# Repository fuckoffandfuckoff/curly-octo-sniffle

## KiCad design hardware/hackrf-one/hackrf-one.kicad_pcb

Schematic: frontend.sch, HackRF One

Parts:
C1, C3, C5, C7, C10, C11, C16, C19, C22, C24, C29, C30, C33, C34, C35, C36, C37, C38, C39, C40, C45, C47, C54, C55, C56, C57, C60, C63, C65, C66, C67: 33pF; GSG-0402; Part Number GRM1555C1H330JA01D
C2, C4, C6, C162, C163: 10nF; GSG-0402; Part Number GRM155R71C103KA01D
C8, C21, C32, C43, C48, C51: 22pF; GSG-0402; Part Number GRM1555C1H220JA01D
C9, C17, C18, C20, C23, C25, C28, C31, C44, C46, C49, C50, C58, C59, C61, C62, C64, C166: 100nF; GSG-0402; Part Number GRM155R61A104KA01D
C12, C13: 330pF; GSG-0402; Part Number GRM155R71H331KA01D
C14: 8p2; GSG-0402; Part Number UMK105CG8R2DV-F
C15: 180pF; GSG-0402; Part Number GRM1555C1H181JA01D
C26, C27: 47pF; GSG-0402; Part Number GRM1555C1H470JA01D
C41, C42, C52, C70, C160: 100pF; GSG-0402; Part Number GRM1555C1H101JA01D
C53, C161, C171: 1uF; GSG-0402; Part Number LMK105BJ105KV-F
D1: GSG-DIODE-TVS-BI; GSG-0402; Part Number LXES15AAA1-100
J2: RF-SHIELD-FRAME; GSG-SHIELD-BMI-S-230; Part Number BMI-S-230-F-R
J3: RF-SHIELD-COVER; GSG-NULL-MODULE; Part Number BMI-S-230-C
J4, J5, J6, J7, J8, J9: MOUNTING_HOLE; GSG-HOLE126MIL-COPPER
J10: GND_CLIP; GSG-TEST-POINT-S1751-46R; Part Number S1751-46R
L1, L4: DNP; GSG-0402
L2, L3, L5, L12, L13: 10uH; GSG-0603; Part Number BRL1608T100M
P4: ANTENNA; GSG-SMA-73251-2120; Part Number 73251-2121
P6: GPO4; GSG-TESTPOINT-50MIL
P7: GPO2; GSG-TESTPOINT-50MIL
P13: GPO1; GSG-TESTPOINT-50MIL
P17: GPO6; GSG-TESTPOINT-50MIL
P19: GPO3; GSG-TESTPOINT-50MIL
P21: REF_IN; GSG-TESTPOINT-50MIL
P27: MIXER_SDATA; GSG-TESTPOINT-50MIL
P31: MIXER_SCLK; GSG-TESTPOINT-50MIL
P32: MIXER_ENX; GSG-TESTPOINT-50MIL
P33: MIXER_RESETX; GSG-TESTPOINT-50MIL
P34: MIX_BYPASS; GSG-TESTPOINT-50MIL
P35: !MIX_BYPASS; GSG-TESTPOINT-50MIL
P42: TX; GSG-TESTPOINT-50MIL
P43: RX; GSG-TESTPOINT-50MIL
P44: HP; GSG-TESTPOINT-50MIL
P45: LP; GSG-TESTPOINT-50MIL
P46: TX_MIX_BP; GSG-TESTPOINT-50MIL
P47: RX_MIX_BP; GSG-TESTPOINT-50MIL
P48: TX_AMP; GSG-TESTPOINT-50MIL
P49: RX_AMP; GSG-TESTPOINT-50MIL
P50: AMP_BYPASS; GSG-TESTPOINT-50MIL
P51: !TX_AMP_PWR; GSG-TESTPOINT-50MIL
P52: !RX_AMP_PWR; GSG-TESTPOINT-50MIL
Q1, Q2, Q4: MOSFET_P; SOT23-3; Part Number BSS84
R1, R2: 470; GSG-0402; Part Number RMCF0402JT470R
R3: 22k; GSG-0402; Part Number ERJ-2GEJ223X
R4: 51k; GSG-0402; Part Number RMCF0402FT51K0
R5, R6, R24, R29, R36: 10k; GSG-0402; Part Number RMCF0402JT10K0
T1: MIX_IN_BALUN; GSG-B0310J50100AHF; Part Number B0310J50100AHF
T2: MIX_OUT_BALUN; GSG-B0310J50100AHF; Part Number B0310J50100AHF
U1, U2, U5, U6, U7, U10, U11: SKY13350; GSG-SKY13350-385LF; Part Number SKY13350-385LF
U3: RX_LOWPASS_FILTER; GSG-LP0603; Part Number LP0603A1880ANTR
U4: RFFC5072; GSG-QFN32; Part Number RFFC5072TR7
U8: RX_HIGHPASS_FILTER; GSG-HP-DEA; Part Number DEA162400HT-8004B1
U9, U12, U14: SKY13317; GSG-SKY13317-373LF; Part Number SKY13317-373LF
U13, U25: MGA-81563; GSG-SOT363; Part Number MGA-81563-TR1G

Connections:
!MIX_BYPASS: C16.1, C38.2, C47.2, P35.1, U1.1, U9.6 (V2), U11.5; also elsewhere on the board
!RX_AMP_PWR: P52.1, Q1.1, R29.2; also elsewhere on the board
!TX_AMP_PWR: P51.1, Q2.1, R24.1; also elsewhere on the board
/frontend/!ANT_BIAS: P13.1, Q4.1, R36.1, U4.15 (GPO1/ADD1)
/frontend/REF_IN: C67.2, C70.1, P21.1, U4.10 (REF_IN)
/frontend/RX_AMP_IN: C58.1, U14.8 (RF3)
/frontend/RX_AMP_OUT: C50.2, U12.4 (RF1)
/frontend/TX_AMP_IN: C59.1, U12.8 (RF3)
/frontend/TX_AMP_OUT: C62.1, U14.4 (RF1)
AMP_BYPASS: C57.1, C65.2, P50.1, U12.6 (V2), U14.6 (V2); also elsewhere on the board
GND: C1.2, C2.2, C3.2, C4.2, C5.2, C6.2, C7.1, C10.1, C11.1, C12.2, C13.2, C16.2, C19.1, C22.1, C24.1, C25.2, C29.2, C30.2, C33.2, C34.2, C35.2, C36.2, C37.2, C38.1, C39.1, C40.1, C41.2, C42.2, C45.1, C47.1, C49.1, C52.2, C53.2, C54.2, C55.2, C56.2, C57.2, C60.1, C63.2, C65.1, C66.1, C70.2, C160.2, C161.2, C162.1, C163.1, C166.2, C171.2, D1.1 (A), J2.0, J4.1, J5.1, J6.1, J7.1, J8.1, J9.1, J10.1, P4.2 (GND), R4.1, U1.3, U2.3, U3.2 (GND), U3.3 (GND), U4.0 (EP), U4.12 (TM), U5.3, U6.3, U7.3, U8.2 (GND), U8.4 (GND), U9.0 (GND), U10.3, U11.3, U12.0 (GND), U13.1, U13.2, U13.4, U13.5, U14.0 (GND), U25.1, U25.2, U25.4, U25.5; also elsewhere on the board
HP: C29.1, C30.1, P44.1, U5.5, U6.1; also elsewhere on the board
LP: C11.2, C19.2, P45.1, U5.1, U6.5; also elsewhere on the board
MIXER_ENX: C35.1, P32.1, R6.2, U4.30 (ENX); also elsewhere on the board
MIXER_RESETX: C34.1, P33.1, R5.2, U4.29 (RESETX); also elsewhere on the board
MIXER_SCLK: C36.1, P31.1, U4.31 (SCLK); also elsewhere on the board
MIXER_SDATA: C37.1, P27.1, U4.32 (SDATA); also elsewhere on the board
MIX_BYPASS: C7.2, C56.1, P34.1, U1.5, U11.1; also elsewhere on the board
MIX_CLK: C67.1; also elsewhere on the board
unnamed: C8.2, U1.6
unnamed: C9.1, U7.2
unnamed: C9.2, U2.2
unnamed: C12.1, R1.2, U4.8 (LFILT3)
unnamed: C13.1, R1.1, R2.2
unnamed: C14.1, C15.1, R2.1, U4.7 (LFITLT2)
unnamed: C14.2, R3.1, U4.6 (LFILT1)
unnamed: C15.2, R3.2
unnamed: C17.1, U3.4 (IN)
unnamed: C17.2, U6.4
unnamed: C18.1, U5.2
unnamed: C18.2, U3.1 (OUT)
unnamed: C20.1, U6.6
unnamed: C20.2, U2.6
unnamed: C21.1, U1.2
unnamed: C21.2, U7.4
unnamed: C23.1, U10.4
unnamed: C23.2, U2.4
unnamed: C25.1, T1.2 (S2)
unnamed: C26.1, U8.3 (OUT)
unnamed: C26.2, U5.4
unnamed: C27.1, U8.1 (IN)
unnamed: C27.2, U6.2
unnamed: C28.1, T1.1 (S1)
unnamed: C28.2, U7.6
unnamed: C31.1, U9.5 (RF2)
unnamed: C31.2, U5.6
unnamed: C32.1, U1.4
unnamed: C32.2, U9.4 (RF1)
unnamed: C43.1, U9.8 (RF3)
unnamed: C43.2, U11.2
unnamed: C44.1, U12.1 (RFC)
unnamed: C44.2, U9.1 (RFC)
unnamed: C46.1, U10.6
unnamed: C46.2, T2.1 (S1)
unnamed: C48.1, U11.6
unnamed: C49.2, T2.2 (S2)
unnamed: C50.1, L5.2, U13.6
unnamed: C51.1, U11.4
unnamed: C51.2, U10.2
unnamed: C58.2, U13.3
unnamed: C59.2, U25.3
unnamed: C61.1, U14.5 (RF2)
unnamed: C61.2, U12.5 (RF2)
unnamed: C62.2, L12.2, U25.6
unnamed: C64.1, U14.1 (RFC)
unnamed: C64.2, D1.2 (K), L13.2, P4.1 (RF)
unnamed: C160.1, C162.2, L12.1, Q2.3
unnamed: C52.1, C163.2, L5.1, Q1.3
unnamed: L1.1, T1.4 (PR2), U4.23 (MIX_IPP)
unnamed: L1.2, T1.3 (PR1), U4.24 (MIX_IPN)
unnamed: L2.1, L4.2, T2.4 (PR2), U4.27 (MIX_OPN)
unnamed: L3.1, L4.1, T2.3 (PR1), U4.28 (MIX_OPP)
unnamed: L13.1, Q4.3
unnamed: P6.1, U4.26 (GPO4/LD/DO)
unnamed: P7.1, U4.16 (GPO2/ADD2)
unnamed: P17.1, U4.9 (MODE/GPO6)
unnamed: P19.1, U4.25 (GPO3/FM)
unnamed: R4.2, U4.4 (REXT)
RX: C10.2, C22.2, C54.1, P43.1, U2.1, U7.1, U10.1; also elsewhere on the board
RX_AMP: C60.2, C66.2, P49.1, U12.3 (V1), U14.7 (V3); also elsewhere on the board
RX_IF: C48.2; also elsewhere on the board
RX_MIX_BP: C40.2, P47.1, U9.7 (V3); also elsewhere on the board
TX: C24.2, C33.1, C45.2, P42.1, U2.5, U7.5, U10.5; also elsewhere on the board
TX_AMP: C55.1, C63.1, P48.1, U12.7 (V3), U14.3 (V1); also elsewhere on the board
TX_IF: C8.1; also elsewhere on the board
TX_MIX_BP: C39.2, P46.1, U9.3 (V1); also elsewhere on the board
VAA: C3.1, C4.1, C5.1, C6.1, C41.1, C42.1, C53.1, C161.1, C166.1, C171.1, L2.2, L3.2, Q1.2, Q2.2, Q4.2, R24.2, R29.1, R36.2, U4.5 (ANA_VDD1), U4.22 (ANA_VDD2); also elsewhere on the board
VCC: C1.1, C2.1, R5.1, R6.1, U4.19 (DIG_VDD); also elsewhere on the board

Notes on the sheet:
amplifier bypass path
switchable image reject filters
Expected MIX_CLK is 1.8 to 3.3 V peak-to-peak at 25 to 52 MHz. It is divided down to 0.5 to 1.5 V (REF_IN).
loop filter
mounting holes are connected to GND
optional alligator clip test point

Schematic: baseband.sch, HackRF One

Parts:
C68, C69, C90, C159, C165, C168: 100pF; GSG-0402; Part Number GRM1555C1H101JA01D
C71, C73, C75, C77, C79, C81, C83, C91, C113, C119, C120, C121, C122, C123, C167: 100nF; GSG-0402; Part Number GRM155R61A104KA01D
C72, C74, C76, C78, C80, C82, C124: 2.2uF; GSG-0402; Part Number LMK105BJ225MV-F
C84, C85, C86, C94, C95, C96, C99, C101, C102, C103, C107, C108, C109, C110: 22pF; GSG-0402; Part Number GRM1555C1H220JA01D
C87, C88, C89, C92, C93: 10nF; GSG-0402; Part Number GRM155R71C103KA01D
C97, C98, C100: 330nF; GSG-0402; Part Number GRM155R61A334KE15D
C104, C111: 3pF; GSG-0402; Part Number GRM1555C1H3R0CA01D
C105: 10uF; GSG-0805; Part Number GRM21BR61A106KE19L
C106: 1uF; GSG-0402; Part Number LMK105BJ105KV-F
C112: 180pF; GSG-0402; Part Number GRM1555C1H181JA01D
C114: 3.3nF; GSG-0402; Part Number GRM155R71H332KA01D
C115: 33pF; GSG-0402; Part Number GRM1555C1H330JA01D
C116: 47pF; GSG-0402; Part Number GRM1555C1H470JA01D
C169, C170: 1.8pF; GSG-0402; Part Number GRM1555C1E1R8BA01D
D3, D9: GSG-DIODE-TVS-BI; GSG-0402; Part Number LXES15AAA1-100
FB2: FILTER; GSG-0805; Part Number BLM21PG221SN1D
L6, L8, L9: DNP; GSG-0402
L7: 6.2nH; GSG-0402; Part Number HK10056N2S-T
NT3: VAA; HEADER-1x2-SHORTED
P2: CLKOUT; GSG-SMA-73251-2120; Part Number 73251-2121
P9: BASEBAND; GSG-HEADER-2x8; Part Number PPPC082LFBN-RC
P14: XCVR_CLKOUT; GSG-TESTPOINT-50MIL
P15: INTR; GSG-TESTPOINT-50MIL
P16: CLKIN; GSG-SMA-73251-2120; Part Number 73251-2121
P18: OEB; GSG-TESTPOINT-50MIL
P37: SCL; GSG-TESTPOINT-50MIL
P38: SDA; GSG-TESTPOINT-50MIL
P39: SSP1_SCK; GSG-TESTPOINT-50MIL
P40: SSP1_COPI; GSG-TESTPOINT-50MIL
P41: SSP1_CIPO; GSG-TESTPOINT-50MIL
P53: CS_XCVR; GSG-TESTPOINT-50MIL
P54: CS_AD; GSG-TESTPOINT-50MIL
P55: TXENABLE; GSG-TESTPOINT-50MIL
P56: RXENABLE; GSG-TESTPOINT-50MIL
P57: XTAL2; GSG-TESTPOINT-50MIL
P58: GCK1; GSG-TESTPOINT-50MIL
P59: GCK2; GSG-TESTPOINT-50MIL
P60: SGPIO_CLK; GSG-TESTPOINT-50MIL
P61: DA0; GSG-TESTPOINT-50MIL
P62: DA7; GSG-TESTPOINT-50MIL
P63: DD0; GSG-TESTPOINT-50MIL
P64: DD9; GSG-TESTPOINT-50MIL
P65: DA4; GSG-TESTPOINT-50MIL
P66: DD5; GSG-TESTPOINT-50MIL
P67: RSSI; GSG-TESTPOINT-50MIL
P83, P84, P85, P86, P87, P88, P89, P90, P91, P92: GND; GSG-TESTPOINT-50MIL
Q3: MOSFET_P; SOT23-3; Part Number DMP2305U-7
R8, R9, R10, R13: 1k; GSG-0402; Part Number RMCF0402FT1K00
R11, R41, R85, R104, R105: 10k; GSG-0402; Part Number RMCF0402JT10K0
R14, R15, R16, R17: 4k7; GSG-0402; Part Number RMCF0402FT4K70
R20, R21, R22, R23: 0; GSG-0402; Part Number RMCF0402ZT0R00
R25, R26: 475; GSG-0402; Part Number RMCF0402JT470R
R27, R28: 1k8; GSG-0402; Part Number RMCF0402JT1K80
R31, R32, R33, R94: 39; GSG-0402; Part Number RMCF0402JT39R0
T3: RX_BALUN; GSG-2500BL14M100; Part Number 2500BL14M100T
T4: TX_BALUN; GSG-2500BL14M100; Part Number 2500BL14M100T
U17: MAX2837; GSG-QFN48-6; Part Number MAX2837ETM+
U18: MAX5864; GSG-QFN48-7; Part Number MAX5864ETM+
U19: SI5351C; GSG-QFN20-4; Part Number SI5351C-B-GM
X1: GSG-XTAL4PIN; GSG-XTAL3.2x2.5mm; Part Number ABM8-25.000MHZ-10-D1G-T

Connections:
!VAA_ENABLE: Q3.1, R11.2; also elsewhere on the board
/baseband/CLK0: R31.2, U19.13 (CLK0)
/baseband/CLK1: R32.2, U19.12 (CLK1)
/baseband/CLK2: R94.2, U19.9 (CLK2)
/baseband/CLK3: R33.2, U19.8 (CLK3)
/baseband/CLK5: C115.1, U19.17 (CLK5)
/baseband/COM: C97.1, U18.47 (COM)
/baseband/CPOUT+: C112.2, R25.1, U17.23 (CPOUT+)
/baseband/CPOUT-: C112.1, R26.1, U17.24 (CPOUT-)
/baseband/IA+: C101.1, C110.1, R20.1, U18.3 (IA+)
/baseband/IA-: C101.2, C109.1, R21.1, U18.4 (IA-)
/baseband/ID+: R13.1, U18.45 (ID+)
/baseband/ID-: R10.1, U18.44 (ID-)
/baseband/INTR: P15.1, R104.2, U19.3 (INTR)
/baseband/OEB: P18.1, R105.2, U19.7 (OEB)
/baseband/QA+: C103.2, C107.1, R23.1, U18.10 (QA+)
/baseband/QA-: C103.1, C108.1, R22.1, U18.9 (QA-)
/baseband/QD+: R8.1, U18.40 (QD+)
/baseband/QD-: R9.1, U18.41 (QD-)
/baseband/REFN: C98.1, U18.48 (REFN)
/baseband/REFP: C100.1, U18.1 (REFP)
/baseband/RXBBI+: P9.7, R20.2, U17.38 (RXBBI+)
/baseband/RXBBI-: P9.5, R21.2, U17.37 (RXBBI-)
/baseband/RXBBQ+: P9.6, R22.2, U17.36 (RXBBQ+)
/baseband/RXBBQ-: P9.4, R23.2, U17.35 (RXBBQ-)
/baseband/TXBBI+: C96.1, P9.12, R10.2, R15.1, U17.43 (TXBBI+)
/baseband/TXBBI-: C96.2, P9.10, R13.2, R14.1, U17.42 (TXBBI-)
/baseband/TXBBQ+: C95.2, P9.11, R9.2, R16.1, U17.44 (TXBBQ+)
/baseband/TXBBQ-: C95.1, P9.13, R8.2, R17.1, U17.45 (TXBBQ-)
/baseband/XA: C170.2, U19.1 (XA), X1.3
/baseband/XB: C169.2, U19.2 (XB), X1.1
/baseband/XCVR_CLKOUT: P14.1, U17.16 (CLOCKOUT)
/baseband/XTAL2: C115.2, C116.1, P57.1, U17.17 (XTAL2)
CLK6: U19.16 (CLK6); also elsewhere on the board
CLKIN: D3.2 (K), P16.1 (RF), R85.1, U19.6 (CLKIN); also elsewhere on the board
CLKOUT: C165.1, D9.2 (K), P2.1 (RF), R33.1; also elsewhere on the board
CS_AD: P54.1, U18.36 (CS); also elsewhere on the board
CS_XCVR: P53.1, U17.30 (CS); also elsewhere on the board
DA0: P61.1, U18.13 (DA0); also elsewhere on the board
DA1: U18.14 (DA1); also elsewhere on the board
DA2: U18.15 (DA2); also elsewhere on the board
DA3: U18.16 (DA3); also elsewhere on the board
DA4: P65.1, U18.19 (DA4); also elsewhere on the board
DA5: U18.20 (DA5); also elsewhere on the board
DA6: U18.21 (DA6); also elsewhere on the board
DA7: P62.1, U18.22 (DA7); also elsewhere on the board
DD0: P63.1, U18.23 (DD0); also elsewhere on the board
DD1: U18.24 (DD1); also elsewhere on the board
DD2: U18.25 (DD2); also elsewhere on the board
DD3: U18.26 (DD3); also elsewhere on the board
DD4: U18.27 (DD4); also elsewhere on the board
DD5: P66.1, U18.28 (DD5); also elsewhere on the board
DD6: U18.29 (DD6); also elsewhere on the board
DD7: U18.30 (DD7); also elsewhere on the board
DD8: U18.31 (DD8); also elsewhere on the board
DD9: P64.1, U18.32 (DD9); also elsewhere on the board
GCK1: C68.1, P58.1, R31.1, U18.6 (CLK); also elsewhere on the board
GCK2: C69.1, P59.1, R32.1; also elsewhere on the board
GND: C68.2, C69.2, C71.2, C72.2, C73.2, C74.2, C75.2, C76.2, C77.2, C78.2, C79.2, C80.2, C81.2, C82.2, C83.2, C84.2, C85.2, C86.2, C87.2, C88.2, C89.2, C90.2, C91.2, C92.2, C93.2, C94.2, C97.2, C98.2, C100.2, C105.2, C106.2, C107.2, C108.2, C109.2, C110.2, C113.2, C116.2, C119.2, C120.2, C121.2, C122.2, C123.2, C124.2, C159.2, C165.2, C167.2, C168.2, C169.1, C170.1, D3.1 (A), D9.1 (A), P2.2 (GND), P9.1, P9.2, P9.3, P9.8, P9.9, P9.14, P9.15, P9.16, P16.2 (GND), P83.1, P84.1, P85.1, P86.1, P87.1, P88.1, P89.1, P90.1, P91.1, P92.1, R14.2, R15.2, R16.2, R17.2, R41.1, R85.2, T3.2 (S2), T3.5 (PM), T4.2 (S2), T4.5 (PM), U17.0 (EP), U17.2 (GNDRXLNA), U17.22 (GNDCP), U17.26 (GNDVCO), U18.0 (EP), U18.5 (GND), U18.7 (GND), U18.12 (GND), U18.17 (OGND), U18.37 (GND), U18.42 (GND), U19.0 (GND), X1.2, X1.4; also elsewhere on the board
MCU_CLK: U19.15 (CLK7); also elsewhere on the board
MIX_CLK: U19.19 (CLK4); also elsewhere on the board
unnamed: C99.1, L7.1, U17.4 (RXRF+)
unnamed: C99.2, L6.1, T3.4 (PR2)
unnamed: C102.1, L7.2, U17.5 (RXRF-)
unnamed: C102.2, L6.2, T3.3 (PR1)
unnamed: C104.1, L9.1, U17.10 (TXRF+)
unnamed: C104.2, L8.1, T4.4 (PR2)
unnamed: C105.1, FB2.2, NT3.2
unnamed: C106.1, U17.27 (BYPASS)
unnamed: C111.1, L9.2, U17.11 (TXRF-)
unnamed: C111.2, L8.2, T4.3 (PR1)
unnamed: C114.1, R26.2
unnamed: C114.2, R25.2
unnamed: FB2.1, Q3.3
RSSI: P67.1, U17.32 (RSSI); also elsewhere on the board
RXENABLE: P56.1, U17.48 (RXENABLE); also elsewhere on the board
RX_IF: T3.1 (S1); also elsewhere on the board
SCL: P37.1, R28.2, U19.4 (SCL); also elsewhere on the board
SDA: P38.1, R27.2, U19.5 (SDA); also elsewhere on the board
SGPIO_CLK: C159.1, P60.1, R94.1; also elsewhere on the board
SSP1_CIPO: C168.1, P41.1, U17.29 (DOUT); also elsewhere on the board
SSP1_COPI: P40.1, U17.31 (DIN), U18.34 (DIN); also elsewhere on the board
SSP1_SCK: P39.1, U17.15 (SCLK), U18.35 (SCLK); also elsewhere on the board
TXENABLE: P55.1, U17.47 (TXENABLE); also elsewhere on the board
TX_IF: T4.1 (S1); also elsewhere on the board
VAA: C71.1, C72.1, C73.1, C74.1, C75.1, C76.1, C77.1, C78.1, C79.1, C80.1, C81.1, C82.1, C83.1, C84.1, C85.1, C86.1, C87.1, C89.1, C90.1, C91.1, C92.1, C93.1, C94.1, NT3.1, U17.1 (VCCRXLNA), U17.7 (VCCTXPAD), U17.13 (VCCTXMX), U17.19 (VCCXTAL), U17.21 (VCCCP), U17.28 (VCCVCO), U17.39 (VCCRXVGA), U17.41 (VCCRXFL), U17.46 (VCCRXMX), U18.2 (VDD), U18.8 (VDD), U18.11 (VDD), U18.33 (VDD), U18.39 (VDD), U18.43 (VDD), U18.46 (REFIN); also elsewhere on the board
VCC: C88.1, C113.1, C119.1, C120.1, C121.1, C122.1, C123.1, C124.1, C167.1, Q3.2, R11.1, R27.1, R28.1, R104.1, R105.1, U17.20 (VCCDIG), U18.18 (OVDD), U19.10 (VDDOB), U19.11 (VDDOA), U19.14 (VDDOD), U19.18 (VDDOC), U19.20 (VDD); also elsewhere on the board
XCVR_EN: R41.2, U17.25 (ENABLE); also elsewhere on the board

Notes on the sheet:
3.3 V CMOS clock output at 10 MHz (or other frequency with firmware modification)
3.3 V CMOS clock input at 10 MHz (or 10 MHz to 100 MHz with firmware modification)
test points
CLK0 is at the sample rate CLK1 is at sample rate x2 CLK2 is at sample rate x2

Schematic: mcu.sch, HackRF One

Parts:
C118, C157, C158, C164: 18pF; GSG-0402; Part Number GRM1555C1H180JA01D
C125: 33pF; GSG-0402; Part Number GRM1555C1H330JA01D
C126, C127, C143, C145, C146: 10uF; GSG-0805; Part Number GRM21BR61A106KE19L
C128, C129, C130, C131, C132, C133, C134, C135, C136, C137, C138, C139, C140, C141, C142, C144, C147, C148, C149, C150, C151, C152, C153, C154: 100nF; GSG-0402; Part Number GRM155R61A104KA01D
C155: DNP; GSG-0805
C156: 47pF; GSG-0402; Part Number GRM1555C1H470JA01D
D2: VAALED; LTST-S220; Part Number LTST-S220KRKT
D4: USBLED; LTST-S220; Part Number LTST-S220KGKT
D5: RXLED; LTST-S220; Part Number LTST-S220KSKT
D6: TXLED; LTST-S220; Part Number LTST-S220KRKT
D7: VCCLED; LTST-S220; Part Number LTST-S220KGKT
D8: 1V8LED; LTST-S220; Part Number LTST-S220KSKT
FB1, FB3: FILTER; GSG-0805; Part Number BLM21PG221SN1D
J1: USB-MICRO-B; GSG-USB-MICROB-FCI-10103592-EXT; Part Number 10103592-0001LF
L10, L11: 4u7; GSG-NRG4026; Part Number NRG4026T4R7M
NT1: 1V8; HEADER-1x2-SHORTED
NT2: VCC; HEADER-1x2-SHORTED
P3: GND; GSG-HEADER-NOMARK-1x2
P5: LEDS; GSG-HEADER-2x3
P20: GPIO; GSG-HEADER-2x11; Part Number PPPC112LFBN-RC
P22: I2S; GSG-HEADER-2x13; Part Number PPPC132LFBN-RC
P23: DBGEN; GSG-TESTPOINT-50MIL
P24: TRST; GSG-TESTPOINT-50MIL
P25: LPC_ISP; GSG-HEADER-1x6
P26: LPC_JTAG; GSG-50MIL-HEADER-2x5-TH; Part Number GRPB052VWVN-RC
P28: SD; GSG-HEADER-2x11; Part Number PPPC112LFBN-RC
P29: CPLD_JTAG; GSG-HEADER-1x2
P30: BANK2_AUX; GSG-HEADER-2x10
P68: SPIFI_CS; GSG-TESTPOINT-50MIL
P69: VREGMODE; GSG-TESTPOINT-50MIL
P70: EN_1V8; GSG-TESTPOINT-50MIL
P71: ID; GSG-TESTPOINT-50MIL
P72, P75, P76, P77, P78, P79: GP_CLKIN; GSG-TESTPOINT-50MIL
P73: P1_2; GSG-TESTPOINT-50MIL
P74: P1_1; GSG-TESTPOINT-50MIL
P80: SHIELD; GSG-HEADER-NOMARK-1x2
P81: SPIFI_SIO2; GSG-TESTPOINT-50MIL
P82: SPIFI_SIO3; GSG-TESTPOINT-50MIL
Q5: MOSFET_P; SOT23-3; Part Number AO3407A
R7, R12, R37, R48, R49, R51, R52, R54, R59, R62, R63, R64, R66, R67, R68, R93: 10k; GSG-0402; Part Number RMCF0402JT10K0
R18, R74: 1k8; GSG-0402; Part Number RMCF0402JT1K80
R19, R30, R34, R77, R78, R79, R80, R81, R86, R87, R88, R89, R90, R91, R96, R98, R99, R100: 39; GSG-0402; Part Number RMCF0402JT39R0
R35: DNP; GSG-0805
R46, R55: 162k; GSG-0402; Part Number RMCF0402FT162K
R47: 330k; GSG-0402; Part Number RMCF0402FT330K
R56: 715k; GSG-0402; Part Number RMCF0402FT715K
R57, R58: 0; GSG-0402; Part Number RMCF0402ZT0R00
R65: 18k; GSG-0402; Part Number RC0402JR-0718KL
R69: 12k; GSG-0402; Part Number MCR01MRTF1202
R72, R75: 470; GSG-0402; Part Number RMCF0402JT470R
R73, R76: 1k; GSG-0402; Part Number RMCF0402FT1K00
SW1: DFU; GSG-SWITCH-FSMRA; Part Number FSMRA3JH
SW2: RESET; GSG-SWITCH-FSMRA; Part Number FSMRA3JH
U15: TVS; GSG-LXES1TBCC2-004; Part Number VBUS54CV-HSF-G4-08
U20: W25Q80; GSG-SOIC8-208; Part Number W25Q80DVSSIG
U21: TPS62410; GSG-S-PVSON-N10; Part Number TPS62410DRCR
U23: LPC4320FBD144; GSG-LQFP144; Part Number LPC4320FBD144,551
U24: GSG-XC2C64A-7VQG100C; GSG-VQ100; Part Number XC2C64A-7VQG100C
X2: MCU_XTAL; GSG-XTAL3.2x2.5mm; Part Number 7V-12.000MAAE-T
X3: RTC_XTAL; GSG-XTAL-AB26TRQ; Part Number AB26TRQ-32.768KHZ-T

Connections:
!MIX_BYPASS: U23.50 (P1_7); also elsewhere on the board
!RX_AMP_PWR: U23.106 (P2_12); also elsewhere on the board
!TX_AMP_PWR: U23.97 (P6_9); also elsewhere on the board
!VAA_ENABLE: P5.5, U23.37 (P5_0); also elsewhere on the board
/mcu/usb/power/ADC0_0: P20.20, U23.6 (ADC0_0/ADC1_0/DAC)
/mcu/usb/power/ADC0_2: P20.16, U23.143 (ADC0_2/ADC1_2)
/mcu/usb/power/ADC0_5: P20.18, U23.144 (ADC0_5/ADC1_5)
/mcu/usb/power/ADC0_6: P20.14, U23.142 (ADC0_6/ADC1_6)
/mcu/usb/power/B1AUX13: P28.16, U24.55 (BANK1F4M13)
/mcu/usb/power/B1AUX14: P28.15, U24.56 (BANK1F4M14)
/mcu/usb/power/B2AUX1: P30.18, U24.13 (BANK2F1M1)
/mcu/usb/power/B2AUX2: P30.17, U24.12 (BANK2F1M2)
/mcu/usb/power/B2AUX3: P30.16, U24.11 (BANK2F1M3)
/mcu/usb/power/B2AUX4: P30.15, U24.10 (BANK2F1M4)
/mcu/usb/power/B2AUX5: P30.14, U24.9 (BANK2F1M5)
/mcu/usb/power/B2AUX6: P30.13, U24.8 (BANK2F1M6)
/mcu/usb/power/B2AUX7: P30.12, U24.7 (BANK2F1M7)
/mcu/usb/power/B2AUX8: P30.11, U24.6 (BANK2F1M8)
/mcu/usb/power/B2AUX9: P30.10, U24.4 (BANK2F1M9)
/mcu/usb/power/B2AUX10: P30.9, U24.3 (BANK2F1M10)
/mcu/usb/power/B2AUX11: P30.8, U24.2 (BANK2F1M11)
/mcu/usb/power/B2AUX12: P30.7, U24.1 (BANK2F1M12)
/mcu/usb/power/B2AUX13: P30.6, U24.99 (BANK2F1M13)
/mcu/usb/power/B2AUX14: P30.5, U24.97 (BANK2F1M14)
/mcu/usb/power/B2AUX15: P30.4, U24.94 (BANK2F1M15)
/mcu/usb/power/B2AUX16: P30.3, U24.92 (BANK2F1M16)
/mcu/usb/power/BANK2F3M1: R77.2, U24.91 (BANK2F3M1)
/mcu/usb/power/BANK2F3M2: P28.18, R78.2, U24.90 (BANK2F3M2)
/mcu/usb/power/BANK2F3M3: R79.2, U24.89 (BANK2F3M3)
/mcu/usb/power/BANK2F3M4: P28.22, R80.2, U24.81 (BANK2F3M4)
/mcu/usb/power/BANK2F3M5: R81.2, U24.79 (BANK2F3M5)
/mcu/usb/power/BANK2F3M6: P28.20, R86.2, U24.78 (BANK2F3M6)
/mcu/usb/power/BANK2F3M7: R87.2, U24.77 (BANK2F3M7)
/mcu/usb/power/BANK2F3M8: R88.2, U24.76 (BANK2F3M8)
/mcu/usb/power/BANK2F3M9: R89.2, U24.74 (BANK2F3M9)
/mcu/usb/power/BANK2F3M10: R90.2, U24.72 (BANK2F3M10)
/mcu/usb/power/BANK2F3M11: R91.2, U24.71 (BANK2F3M11)
/mcu/usb/power/BANK2F3M12: P28.21, R96.2, U24.70 (BANK2F3M12)
/mcu/usb/power/BANK2F3M14: R98.2, U24.67 (BANK2F3M14)
/mcu/usb/power/BANK2F3M15: R99.2, U24.64 (BANK2F3M15)
/mcu/usb/power/BANK2F3M16: R100.2, U24.61 (BANK2F3M16)
/mcu/usb/power/CPLD_TCK: P28.17, U23.74 (P6_1), U24.48 (TCK)
/mcu/usb/power/CPLD_TDI: P28.19, U23.78 (P6_2), U24.45 (TDI)
/mcu/usb/power/CPLD_TDO: P29.2, U23.69 (P9_5), U24.83 (TDO)
/mcu/usb/power/CPLD_TMS: P29.1, U23.82 (P6_5), U24.47 (TMS)
/mcu/usb/power/DBGEN: P23.1, R64.1, U23.28 (DBGEN)
/mcu/usb/power/DM: R58.1, U23.20 (USB0_DM)
/mcu/usb/power/DP: R57.1, U23.18 (USB0_DP)
/mcu/usb/power/EN1V8: P70.1, R54.2, R76.2, U21.9 (EN2), U23.100 (P6_10)
/mcu/usb/power/GCK0: P30.19, U24.22 (BANK1F2M7)
/mcu/usb/power/GPIO3_8: P20.5, U23.110 (P7_0)
/mcu/usb/power/GPIO3_9: P20.6, U23.113 (P7_1)
/mcu/usb/power/GPIO3_10: P20.7, U23.115 (P7_2)
/mcu/usb/power/GPIO3_11: P20.8, U23.117 (P7_3)
/mcu/usb/power/GPIO3_12: P20.9, U23.132 (P7_4)
/mcu/usb/power/GPIO3_13: P20.10, U23.133 (P7_5)
/mcu/usb/power/GPIO3_14: P20.11, U23.134 (P7_6)
/mcu/usb/power/GPIO3_15: P20.12, U23.140 (P7_7)
/mcu/usb/power/GP_CLKIN: C156.1, P72.1, R34.1, U23.14 (P4_7)
/mcu/usb/power/I2C1_SCL: P22.5, U23.88 (P2_4)
/mcu/usb/power/I2C1_SDA: P22.6, U23.87 (P2_3)
/mcu/usb/power/I2S0_RX_MCLK: P22.14, U23.73 (P6_0)
/mcu/usb/power/I2S0_RX_SCK: P22.12, U23.120 (PF_4)
/mcu/usb/power/I2S0_RX_SDA: P22.13, U23.116 (P3_2)
/mcu/usb/power/I2S0_RX_WS: P22.15, U23.114 (P3_1)
/mcu/usb/power/I2S0_TX_MCLK: P22.17, U23.99 (CLK2)
/mcu/usb/power/I2S0_TX_SCK: P22.16, U23.112 (P3_0)
/mcu/usb/power/ISP: P25.2, R59.2, U23.96 (P2_7)
/mcu/usb/power/LED1: P5.3, R72.2, U23.3 (P4_1)
/mcu/usb/power/LED2: P5.4, R73.2, U23.8 (P4_2)
/mcu/usb/power/LED3: P5.6, R74.2, U23.103 (P6_12)
/mcu/usb/power/P1_1: P74.1, R67.1, U23.42 (P1_1)
/mcu/usb/power/P1_2: P73.1, R68.1, U23.43 (P1_2)
/mcu/usb/power/P2_8: P22.23, R30.1, U23.98 (P2_8)
/mcu/usb/power/P2_9: P22.21, R93.1, U23.102 (P2_9)
/mcu/usb/power/P2_13: P22.22, U23.108 (P2_13)
/mcu/usb/power/REG_OUT1: C145.2, C146.2, L11.1, NT2.2, R56.1, U21.4 (FB1)
/mcu/usb/power/REG_OUT2: C125.1, C126.1, C127.1, L10.2, NT1.2, R47.1
/mcu/usb/power/RESET: P22.3, P25.6, P26.10, R19.1, U23.128 (RESET)
/mcu/usb/power/RREF: R69.1, U23.24 (USB0_RREF)
/mcu/usb/power/RTCX1: C118.1, U23.125 (RTCX1), X3.2
/mcu/usb/power/RTCX2: C164.1, U23.126 (RTCX2), X3.1
/mcu/usb/power/RTC_ALARM: P20.2, U23.129 (RTC_ALARM)
/mcu/usb/power/SD_CD: P28.3, U23.60 (P1_13)
/mcu/usb/power/SD_CLK: P28.11, U23.45 (CLK0)
/mcu/usb/power/SD_CMD: P28.9, U23.49 (P1_6)
/mcu/usb/power/SD_DAT0: P28.7, U23.52 (P1_9)
/mcu/usb/power/SD_DAT1: P28.6, U23.53 (P1_10)
/mcu/usb/power/SD_DAT2: P28.5, U23.55 (P1_11)
/mcu/usb/power/SD_DAT3: P28.4, U23.56 (P1_12)
/mcu/usb/power/SD_POW: P28.10, U23.48 (P1_5)
/mcu/usb/power/SD_VOLT0: P28.8, U23.51 (P1_8)
/mcu/usb/power/SGPIO0: P75.1, R79.1, U23.32 (P0_0)
/mcu/usb/power/SGPIO1: R81.1, U23.34 (P0_1)
/mcu/usb/power/SGPIO2: R89.1, U23.62 (P1_15)
/mcu/usb/power/SGPIO3: R90.1, U23.64 (P1_16)
/mcu/usb/power/SGPIO4: R98.1, U23.79 (P6_3)
/mcu/usb/power/SGPIO5: R99.1, U23.83 (P6_6)
/mcu/usb/power/SGPIO6: R100.1, U23.84 (P2_2)
/mcu/usb/power/SGPIO7: P76.1, R87.1, U23.38 (P1_0)
/mcu/usb/power/SGPIO9: P77.1, R77.1, U23.7 (P4_3)
/mcu/usb/power/SGPIO10: P78.1, R88.1, U23.61 (P1_14)
/mcu/usb/power/SGPIO11: P79.1, R91.1, U23.66 (P1_17)
/mcu/usb/power/SGPIO12: R96.1, U23.67 (P1_18)
/mcu/usb/power/SGPIO13: R78.1, U23.15 (P4_8)
/mcu/usb/power/SGPIO14: R80.1, U23.33 (P4_9)
/mcu/usb/power/SGPIO15: R86.1, U23.35 (P4_10)
/mcu/usb/power/SPIFI_CIPO: P22.7, U20.2 (DO), U23.122 (P3_6)
/mcu/usb/power/SPIFI_COPI: P22.9, U20.5 (DI), U23.123 (P3_7)
/mcu/usb/power/SPIFI_CS: P68.1, U20.1 (CS), U23.124 (P3_8)
/mcu/usb/power/SPIFI_SCK: P22.8, U20.6 (CLK), U23.118 (P3_3)
/mcu/usb/power/SPIFI_SIO2: P81.1, U20.3 (WP), U23.121 (P3_5)
/mcu/usb/power/SPIFI_SIO3: P82.1, U20.7 (HOLD), U23.119 (P3_4)
/mcu/usb/power/TCK: P26.4, R66.2, U23.27 (TCK/SWDCLK)
/mcu/usb/power/TDI: P26.8, U23.26 (TDI)
/mcu/usb/power/TDO: P26.6, R63.1, U23.31 (TDO/SWO)
/mcu/usb/power/TMS: P26.2, U23.30 (TMS/SWDIO)
/mcu/usb/power/U0_RXD: P22.19, P25.4, U23.81 (P2_1)
/mcu/usb/power/U0_TXD: P22.20, P25.5, U23.75 (P2_0)
/mcu/usb/power/USB_SHIELD: C155.1, J1.0 (SHIELD), P80.1, P80.2, R35.1
/mcu/usb/power/VBAT: C136.1, P20.1, U23.127 (VBAT)
/mcu/usb/power/VBUS: FB1.2, P20.21, Q5.2, R62.2, U15.5 (VDD)
/mcu/usb/power/VBUSCTRL: P20.17, Q5.1, R37.2
/mcu/usb/power/VIN: C143.1, C147.1, P20.22, Q5.3, R52.1, U21.3 (VIN)
/mcu/usb/power/VREGMODE: P69.1, R51.2, U23.101 (P6_11)
/mcu/usb/power/WAKEUP: P20.4, R48.2, U23.130 (WAKEUP0)
/mcu/usb/power/XTAL1: C157.1, U23.12 (XTAL1), X2.1
/mcu/usb/power/XTAL2: C158.1, U23.13 (XTAL2), X2.3
AMP_BYPASS: U23.104 (P2_10); also elsewhere on the board
CLK6: P22.25; also elsewhere on the board
CLKIN: P22.2; also elsewhere on the board
CLKOUT: P22.1; also elsewhere on the board
CS_AD: U23.65 (P5_7); also elsewhere on the board
CS_XCVR: U23.70 (P1_20); also elsewhere on the board
DA0: U24.43 (BANK1F4M8); also elsewhere on the board
DA1: U24.42 (BANK1F4M7); also elsewhere on the board
DA2: U24.41 (BANK1F4M6); also elsewhere on the board
DA3: U24.40 (BANK1F4M5); also elsewhere on the board
DA4: U24.39 (BANK1F4M4); also elsewhere on the board
DA5: U24.37 (BANK1F4M3); also elsewhere on the board
DA6: U24.36 (BANK1F4M2); also elsewhere on the board
DA7: U24.35 (BANK1F4M1); also elsewhere on the board
DD0: U24.34 (BANK1F2M16); also elsewhere on the board
DD1: U24.33 (BANK1F2M15); also elsewhere on the board
DD2: U24.32 (BANK1F2M14); also elsewhere on the board
DD3: U24.30 (BANK1F2M13); also elsewhere on the board
DD4: U24.29 (BANK1F2M12); also elsewhere on the board
DD5: U24.28 (BANK1F2M11); also elsewhere on the board
DD6: U24.24 (BANK1F2M9); also elsewhere on the board
DD7: U24.19 (BANK1F2M6); also elsewhere on the board
DD8: U24.18 (BANK1F2M5); also elsewhere on the board
DD9: U24.17 (BANK1F2M4); also elsewhere on the board
GCK1: P28.14, U24.23 (BANK1F2M8); also elsewhere on the board
GCK2: P28.13, U24.27 (BANK1F2M10); also elsewhere on the board
GND: C118.2, C126.2, C127.2, C128.2, C129.2, C130.2, C131.2, C132.2, C133.2, C134.2, C135.2, C136.2, C137.2, C138.2, C139.2, C140.2, C141.2, C142.2, C143.2, C144.2, C145.1, C146.1, C147.2, C148.2, C149.2, C150.2, C151.2, C152.2, C153.2, C154.2, C155.2, C156.2, C157.2, C158.2, C164.2, D2.1 (K), D4.1 (K), D5.1 (K), D6.1 (K), D7.1 (K), D8.1 (K), FB3.2, P3.1, P3.2, P5.1, P20.13, P20.15, P20.19, P22.4, P22.10, P22.18, P25.1, P26.3, P26.5, P26.9, P28.2, P28.12, P30.2, P30.20, R7.2, R35.2, R37.1, R46.1, R54.1, R55.1, R65.1, R68.2, R69.2, R93.2, SW1.0 (SHIELD), SW2.0 (SHIELD), SW2.1, U15.2 (GND), U20.4 (GND), U21.0 (PP), U21.8 (GND), U23.4 (VSSIO), U23.19 (USB0_VSSA_TERM), U23.23 (USB0_VSSA_REF), U23.40 (VSSIO), U23.76 (VSSIO), U23.109 (VSSIO), U23.135 (VSSA), U23.139 (ADC0_3/ADC1_3), U24.21 (GND), U24.31 (GND), U24.62 (GND), U24.69 (GND), U24.84 (GND), U24.100 (GND), X2.2, X2.4; also elsewhere on the board
HP: U23.1 (P4_0); also elsewhere on the board
LP: U23.39 (P5_1); also elsewhere on the board
MCU_CLK: R34.2; also elsewhere on the board
MIXER_ENX: U23.57 (P5_4); also elsewhere on the board
MIXER_RESETX: U23.58 (P5_5); also elsewhere on the board
MIXER_SCLK: U23.95 (P2_6); also elsewhere on the board
MIXER_SDATA: U23.80 (P6_4); also elsewhere on the board
MIX_BYPASS: U23.86 (P6_8); also elsewhere on the board
unnamed: C125.2, R46.2, R47.2, U21.1 (ADJ2)
unnamed: D2.2 (A), R18.1
unnamed: D4.2 (A), R72.1
unnamed: D5.2 (A), R73.1
unnamed: D6.2 (A), R74.1
unnamed: D7.2 (A), R75.1
unnamed: D8.2 (A), R76.1
unnamed: FB1.1, J1.1 (VBUS)
unnamed: FB3.1, J1.5 (GND)
unnamed: J1.2 (D-), R58.2, U15.3 (ESD2)
unnamed: J1.3 (D+), R57.2, U15.1 (ESD1)
unnamed: J1.4 (ID), P71.1, R12.2, U23.22 (USB0_ID)
unnamed: L10.1, U21.10 (SW2)
unnamed: L11.2, U21.6 (SW1)
unnamed: P24.1, U23.29 (TRST)
unnamed: R19.2, R49.2, SW2.2
unnamed: R7.1, R30.2, SW1.2
unnamed: R51.1, U21.2 (MODE/DATA)
unnamed: R52.2, U21.7 (EN1)
unnamed: R55.2, R56.2, U21.5 (DEF1)
unnamed: R62.1, R65.2, U23.21 (USB0_VBUS)
RSSI: U23.2 (ADC0_1/ADC1_1); also elsewhere on the board
RX: U23.91 (P2_5); also elsewhere on the board
RXENABLE: U23.10 (P4_5); also elsewhere on the board
RX_AMP: U23.105 (P2_11); also elsewhere on the board
RX_MIX_BP: U23.54 (P5_3); also elsewhere on the board
SCL: P22.26, U23.92 (I2C0_SCL); also elsewhere on the board
SDA: P22.24, U23.93 (I2C0_SDA); also elsewhere on the board
SGPIO_CLK: U23.72 (P9_6); also elsewhere on the board
SSP1_CIPO: U23.44 (P1_3); also elsewhere on the board
SSP1_COPI: U23.47 (P1_4); also elsewhere on the board
SSP1_SCK: U23.68 (P1_19); also elsewhere on the board
TX: U23.85 (P6_7); also elsewhere on the board
TXENABLE: U23.9 (P4_4); also elsewhere on the board
TX_AMP: U23.63 (P5_6); also elsewhere on the board
TX_MIX_BP: U23.46 (P5_2); also elsewhere on the board
VAA: R18.2; also elsewhere on the board
VCC: C128.1, C129.1, C130.1, C131.1, C132.1, C133.1, C134.1, C135.1, C137.1, C138.1, C139.1, C140.1, C141.1, C142.1, C144.1, C148.1, C149.1, C150.1, C153.1, C154.1, NT2.1, P5.2, P20.3, P22.11, P26.1, P28.1, P30.1, R12.1, R48.1, R49.1, R59.1, R63.2, R64.2, R66.1, R67.2, R75.2, SW1.1, U20.8 (VCC), U23.5 (VDDIO), U23.16 (USB0_VDDA3V3_DRIVER), U23.17 (USB0_VDDA3V3), U23.25 (VDDREG), U23.36 (VDDIO), U23.41 (VDDIO), U23.59 (VDDREG), U23.71 (VDDIO), U23.77 (VDDIO), U23.94 (VDDREG), U23.107 (VDDIO), U23.111 (VDDIO), U23.131 (VDDREG), U23.136 (ADC0_7/ADC1_7), U23.137 (VDDA), U23.138 (ADC0_4/ADC1_4), U23.141 (VDDIO), U24.5 (VAUX), U24.38 (VCCIO1), U24.51 (VCCIO1), U24.88 (VCCIO2), U24.98 (VCCIO2); also elsewhere on the board
XCVR_EN: U23.11 (P4_6); also elsewhere on the board

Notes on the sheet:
Cortex Debug Connector (10 pin 50 mil)
U23 starts up on this 12 MHz crystal. This makes it possible to use USB0 DFU boot mode. It should be possible to switch to GP_CLKIN provided by the clock generator IC (MCL_CLK) if desired.
GND
VCC
P1_1
P1_2
P2_8
P2_9
USART3
SSP0
USB0
SPIFI
USART0
Boot selection:
Default boot configuration is SPIFI. Press SW1 during reset to switch to USB0 (DFU mode).
Series resistors are here because of a possible overshoot/undershoot problem. They may be able to be removed safely. Anyway, they probably will minimize damage in the event of SGPIO/CPLD misconfiguration.
/I2S0_TX_WS
I2S0_TX_SDA/
See also I2S0 pins on P20.
pin straps for hardware version detection

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
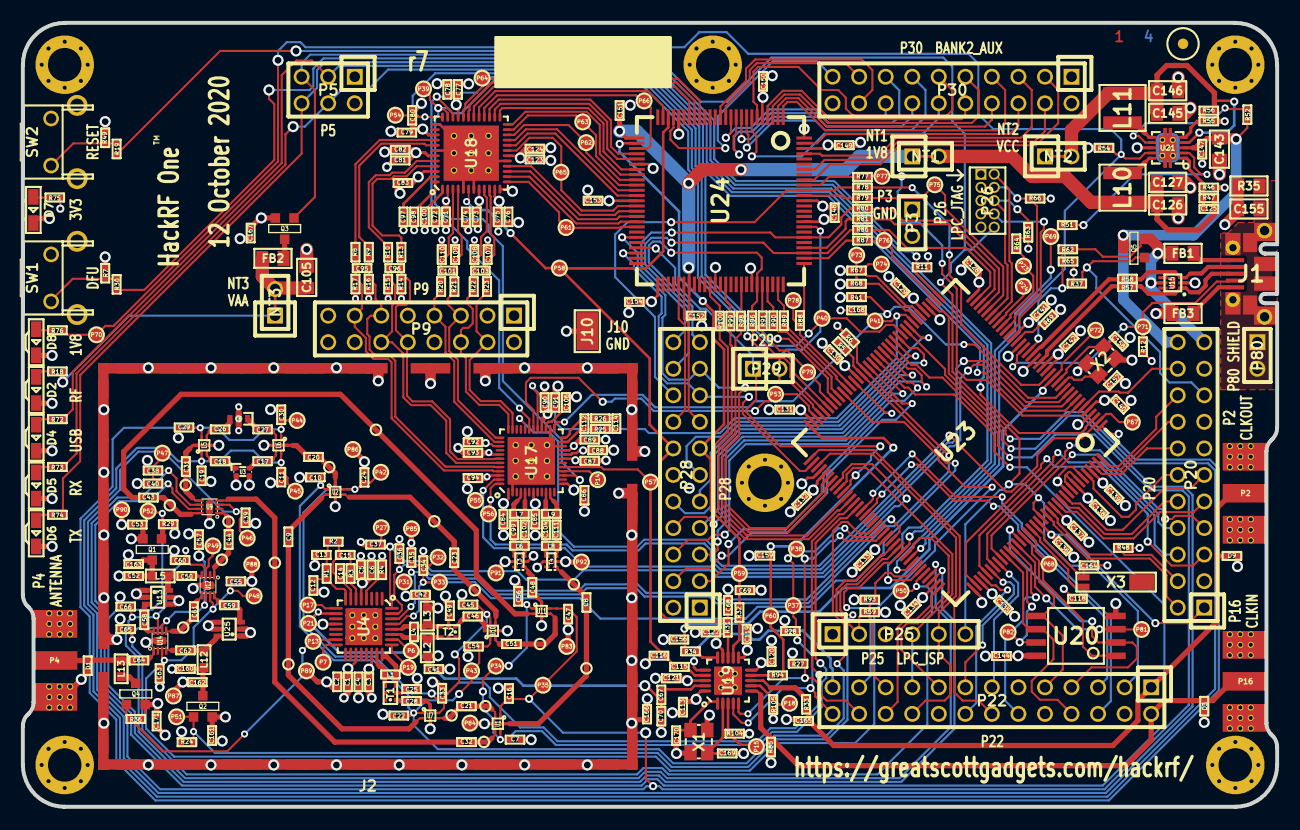
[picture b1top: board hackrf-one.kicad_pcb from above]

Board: 4 copper layers, 120.0 x 75.0 mm, 432 parts (0 on the bottom side), 316 nets.

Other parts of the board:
MARK1MM: VAL**; GSG-MARK1MM
TESTPOINT-30MIL-MASKONLY, TESTPOINT-30MIL-MASKONLY#2, TESTPOINT-30MIL-MASKONLY#3, TESTPOINT-30MIL-MASKONLY#4, TESTPOINT-30MIL-MASKONLY#5, TESTPOINT-30MIL-MASKONLY#6, TESTPOINT-30MIL-MASKONLY#7, TESTPOINT-30MIL-MASKONLY#8, TESTPOINT-30MIL-MASKONLY#9, TESTPOINT-30MIL-MASKONLY#10, TESTPOINT-30MIL-MASKONLY#11, TESTPOINT-30MIL-MASKONLY#12, TESTPOINT-30MIL-MASKONLY#13, TESTPOINT-30MIL-MASKONLY#14, TESTPOINT-30MIL-MASKONLY#15, TESTPOINT-30MIL-MASKONLY#16, TESTPOINT-30MIL-MASKONLY#17: VAL**; GSG-TESTPOINT-30MIL-MASKONLY

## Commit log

2018-11-12 HackRF One: changed U25 TX RF amplifier from MGA-81563 to TRF37A73
2018-11-12 HackRF One: changed U13 RX RF amplifier from MGA-81563 to TRF37D73
2018-11-12 HackRF One: replaced Q4 antenna port power FET with U16 current-limited power switch
2018-11-12 HackRF One: replaced NRND GRM155R61A104KA01D 100 nF capacitors with GCM155R71C104KA55
2018-11-12 HackRF One: replaced NRND GRM1555C1H330JA01D 33 pF capacitors with GCM1555C1H330JA16
2018-11-12 HackRF One: replaced EoL GRM21BR61A106KE19L 10 uF capacitors with GRM21BR61C106KE15
2018-11-12 HackRF One: replaced obsolete NRG4026T4R7M 4.7 uH inductors with NRS4018T4R7MDGJ
2018-11-12 HackRF One: replaced obsolete LXES15AAA1-100 TVS diode with LXES15AAA1-153
2018-11-12 HackRF One: replaced EoL SKY13350-385LF RF switch with SKY13453-385LF
2018-11-12 HackRF One: changed VBUS voltage divider to match GreatFET One
2018-11-12 HackRF One: added ADC pin straps for hardware version detection
2018-11-13 HackRF One: updated layout to match recent changes to schematic
2018-11-14 HackRF One: prefer Murata balun for T3 and T4
2018-11-14 HackRF One: replaced R69 for part availability
2018-11-15 HackRF One: replaced various capacitors that are NRND
2018-11-23 HackRF One: corrected R65 part selection
2018-12-07 temporary firmware changes for HackRF One r5 switch control
2020-10-12 HackRF One: update plot parameters
2020-10-12 HackRF One: add impedance requirement
2020-10-12 HackRF One: update license to CERN-OHL-P v2
2020-10-12 travis: use newer OSX image to fix bundle error
2020-10-12 HackRF One: add ADC pin straps for hardware version detection
    update power supply schematic symbols
2020-10-12 HackRF One: update silkscreen
2020-10-12 HackRF One: update title block dates
2020-10-12 HackRF One: update VBUS sense resistor values

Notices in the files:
hardware/hackrf-one/baseband.sch:
Copyright 2012-2020 Great Scott Gadgets
Licensed under the CERN-OHL-P v2
